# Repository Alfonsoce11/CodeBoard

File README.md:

# CodeBoard
A keyboard specially made for coding with quicker access to common characters. After making [CodePad](https://github.com/Alfonsoce11/CodePad/) I figured the next logical thing to do was to make a full keyboard for coding.
| Assembly | Exploded View |
|--|--|
|  |  |

# Layout

I chose this layout so that I could keep the normal keyboard layout while also optimizing for coding. It has keys I often use while coding to the right of the main part of the keyboard, similar to a numpad but for coding. The brackets and quotes type both characters and put the curser between the characters. The angle brackets don't because they are more commonly used for conditions rather than brackets in coding.

I wrote the firmware using KMK.

# Case

The case consists of 3 parts: the bottom, the plate, and the top part. It uses M3x16mm screws and heat-set inserts to hold the 3 parts together.
| Bottom | Plate | Top |
|--------|-------|-----|
|  |  |  |

Heres an assembly of the case:

I made the case using OnShape.

# PCB

**Schematic:**

**PCB:**

**3D PCB:**

I made the PCB on KiCAD and learned how to create a key matrix.

# More Views

# BOM
|Item                           |Quantity|Price |Link                                                                                                                                                                                                                                                           |
|-------------------------------|--------|------|---------------------------------------------------------------------------------------------------------------------------------------------------------------------------------------------------------------------------------------------------------------|
|Raspberry Pi Pico              |1       |$4.00 |https://vilros.com/products/raspberry-pi-pico                                                                                                                                                                                                                  |
|Brown 90 PCS Cherry MX Switches|1       |$16.01|https://www.aliexpress.com/item/3256807797357274.html?spm=a2g0o.cart.0.0.7b1f38daq82dup&mp=1&pdp_npi=5%40dis%21USD%21USD%2034.20%21USD%2016.01%21%21USD%2016.01%21%21%21%402101c59517507203853198392e81ba%2112000043155900936%21ct%21US%216400114757%21%211%210|
|M3x16mm 50 PCS Screws          |1       |$3.10 |https://www.aliexpress.com/item/2251832772825104.html?spm=a2g0o.cart.0.0.7b1f38daq82dup&mp=1&pdp_npi=5%40dis%21USD%21USD%203.10%21USD%203.10%21%21USD%203.10%21%21%21%402101c59517507203853198392e81ba%2166368903760%21ct%21US%216400114757%21%211%210         |
|Heat Set Inserts               |1       |$6.55 |https://www.aliexpress.com/item/2255800046543591.html?spm=a2g0o.cart.0.0.7b1f38daq82dup&mp=1&pdp_npi=5%40dis%21USD%21USD%207.10%21USD%206.55%21%21USD%206.55%21%21%21%402101c59517507203853198392e81ba%2110000000945302188%21ct%21US%216400114757%21%211%210   |
|100 PCS Diodes                 |1       |$1.46 |https://www.aliexpress.com/item/2255799955957794.html?spm=a2g0o.cart.0.0.7b1f38daq82dup&mp=1&pdp_npi=5%40dis%21USD%21USD%201.46%21USD%201.46%21%21USD%201.46%21%21%21%402101c59517507203853198392e81ba%2110000000428321629%21ct%21US%216400114757%21%211%210   |
|100 PCS Black Keycaps          |1       |$22.03|https://www.aliexpress.com/item/3256805981338445.html?spm=a2g0o.cart.0.0.7b1f38daq82dup&mp=1&pdp_npi=5%40dis%21USD%21USD%2030.60%21USD%2022.03%21%21USD%2022.03%21%21%21%402101c59517507203853198392e81ba%2112000036085970239%21ct%21US%216400114757%21%211%210|
|2u Cherry Stabilizers          |2       |$1.55 |https://www.aliexpress.com/item/2251832678459913.html?spm=a2g0o.cart.0.0.7b1f38daq82dup&mp=1&pdp_npi=5%40dis%21USD%21USD%201.87%21USD%201.55%21%21USD%201.55%21%21%21%402101c59517507203853198392e81ba%2112000036652220667%21ct%21US%216400114757%21%212%210   |
|6u Cherry Stabilizer           |1       |$1.66 |https://www.aliexpress.com/item/2251832678459913.html?spm=a2g0o.cart.0.0.7b1f38daq82dup&mp=1&pdp_npi=5%40dis%21USD%21USD%202.00%21USD%201.66%21%21USD%201.66%21%21%21%402101c59517507203853198392e81ba%2112000036652220673%21ct%21US%216400114757%21%211%210   |
|PCB                            |5       |$25.11|https://jlcpcb.com/                                                                                                                                                                                                                                            |
|TOTAL                          |        |$81.47|                                                                                                                                                                                                                                                               |

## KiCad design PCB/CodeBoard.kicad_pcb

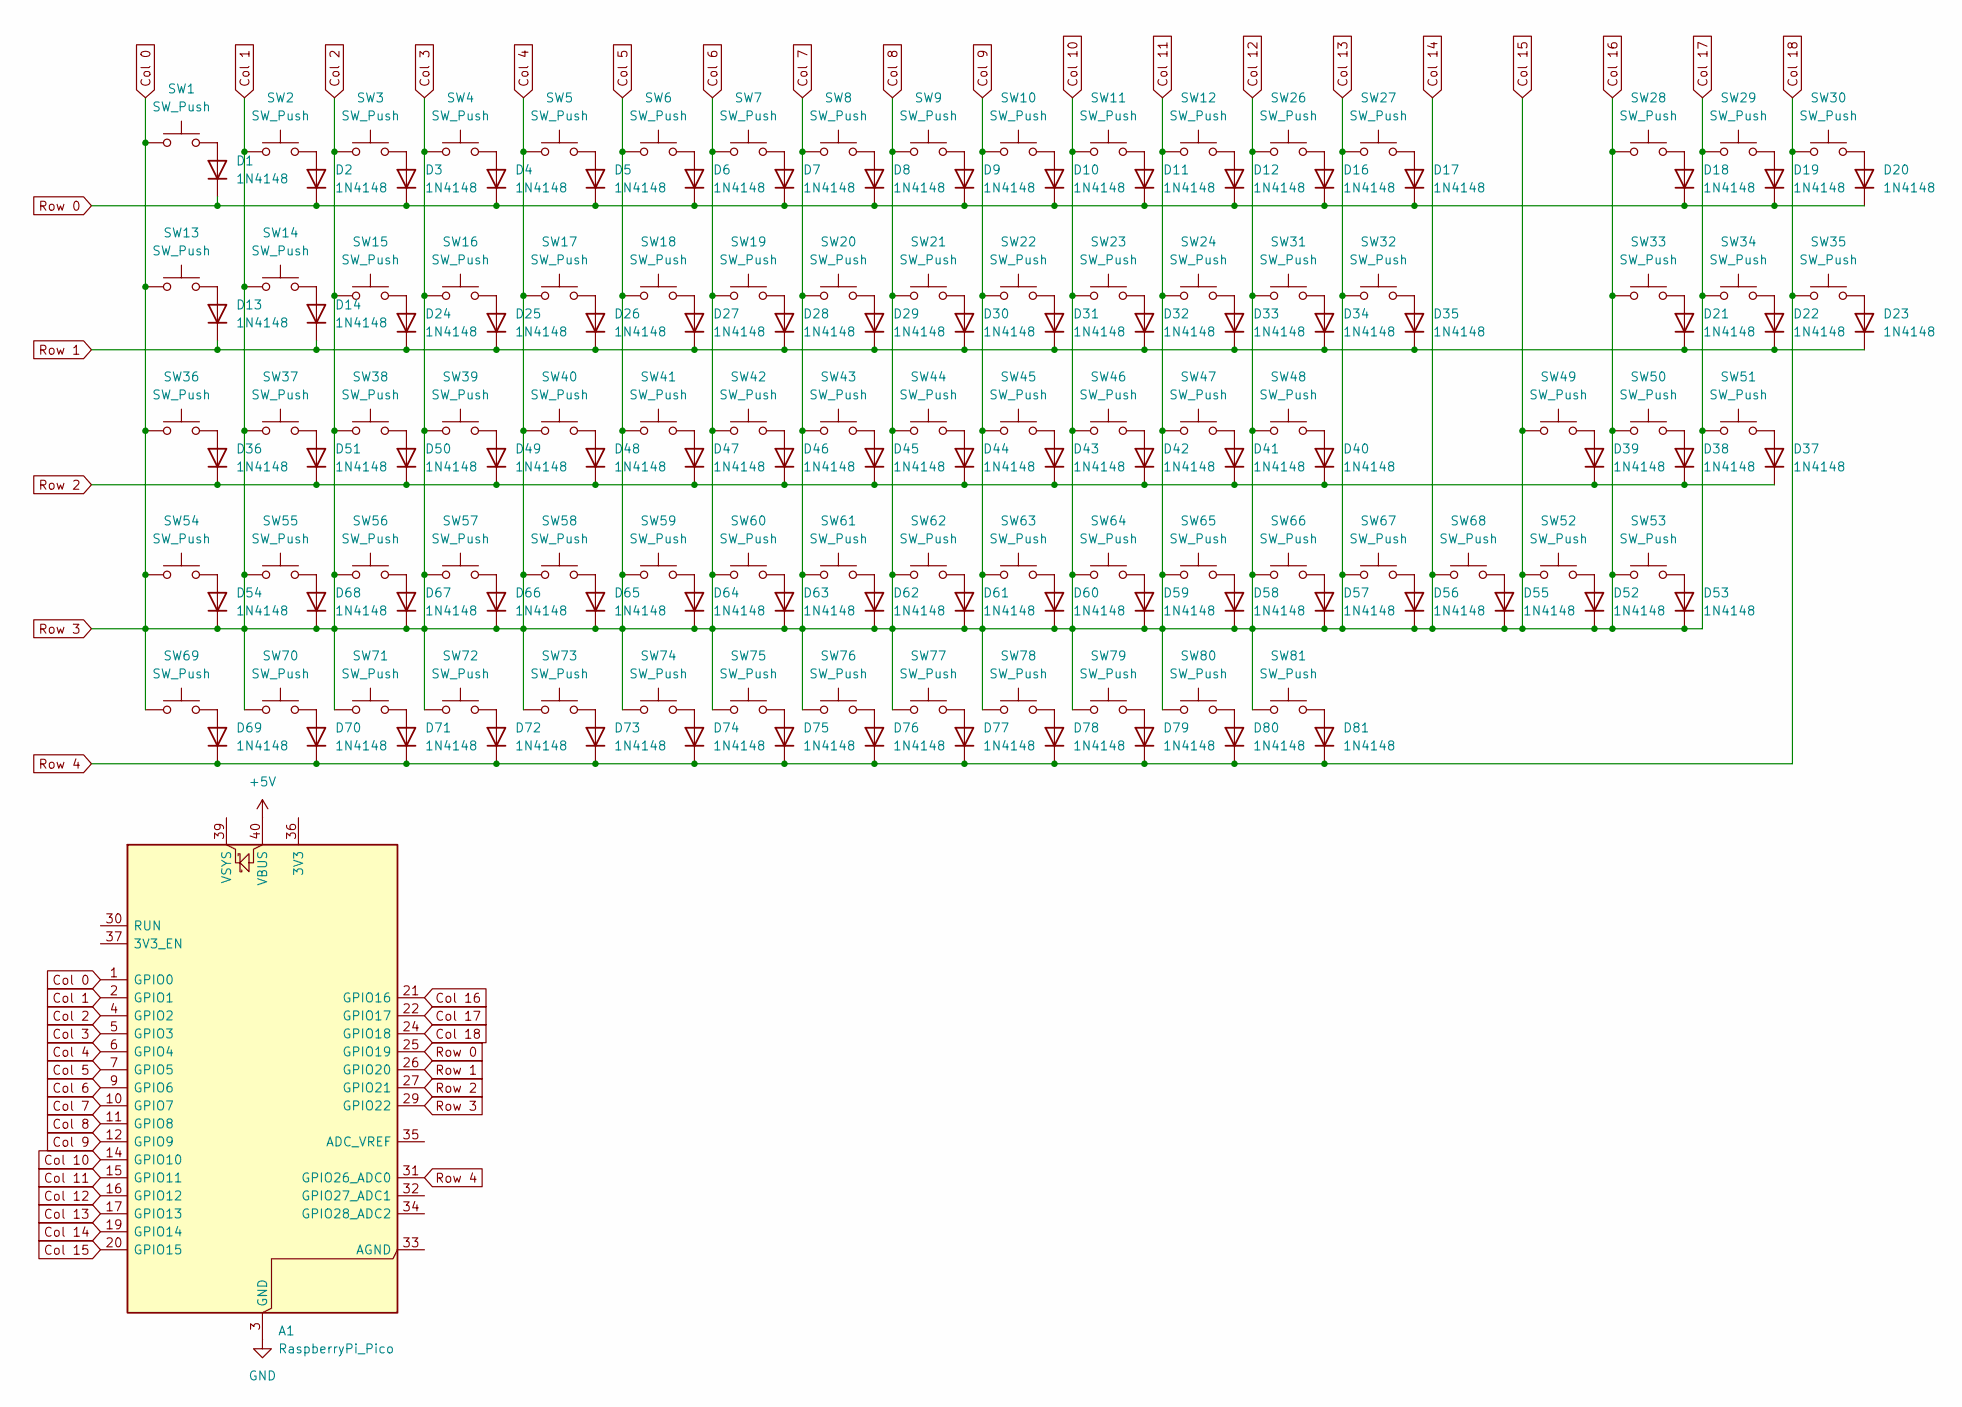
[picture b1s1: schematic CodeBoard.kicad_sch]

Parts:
A1: RaspberryPi_Pico; RaspberryPi_Pico_Common_Unspecified
D1, D2, D3, D4, D5, D6, D7, D8, D9, D10, D11, D12, D13, D14, D16, D17, D18, D19, D20, D21, D22, D23, D24, D25, D26, D27, D28, D29, D30, D31, D32, D33, D34, D35, D36, D37, D38, D39, D40, D41, D42, D43, D44, D45, D46, D47, D48, D49, D50, D51, D52, D53, D54, D55, D56, D57, D58, D59, D60, D61, D62, D63, D64, D65, D66, D67, D68, D69, D70, D71, D72, D73, D74, D75, D76, D77, D78, D79, D80, D81: 1N4148; D_DO-35_SOD27_P7.62mm_Horizontal
SW1, SW2, SW3, SW4, SW5, SW6, SW7, SW8, SW9, SW10, SW11, SW12, SW13, SW14, SW15, SW16, SW17, SW18, SW19, SW20, SW21, SW22, SW23, SW24, SW26, SW27, SW28, SW29, SW30, SW31, SW32, SW33, SW34, SW35, SW36, SW37, SW38, SW39, SW40, SW41, SW42, SW43, SW44, SW45, SW46, SW47, SW48, SW49, SW50, SW51, SW52, SW53, SW54, SW55, SW56, SW57, SW58, SW59, SW60, SW61, SW62, SW63, SW64, SW65, SW66, SW67, SW68, SW69, SW70, SW71, SW72, SW73, SW74, SW75, SW76, SW77, SW78, SW79, SW80, SW81: SW_Push; SW_Cherry_MX_1.00u_PCB

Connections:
+5V: A1.40 (VBUS)
Col 0: A1.1 (GPIO0), A1.2 (GPIO1), A1.4 (GPIO2), A1.5 (GPIO3), A1.6 (GPIO4), A1.7 (GPIO5), A1.9 (GPIO6), A1.10 (GPIO7), A1.11 (GPIO8), A1.12 (GPIO9), A1.14 (GPIO10), A1.15 (GPIO11), A1.16 (GPIO12), A1.17 (GPIO13), A1.19 (GPIO14), A1.20 (GPIO15), A1.21 (GPIO16), A1.22 (GPIO17), A1.29 (GPIO22), D52.1 (K), D53.1 (K), D54.1 (K), D55.1 (K), D56.1 (K), D57.1 (K), D58.1 (K), D59.1 (K), D60.1 (K), D61.1 (K), D62.1 (K), D63.1 (K), D64.1 (K), D65.1 (K), D66.1 (K), D67.1 (K), D68.1 (K), SW1.1, SW2.1, SW3.1, SW4.1, SW5.1, SW6.1, SW7.1, SW8.1, SW9.1, SW10.1, SW11.1, SW12.1, SW13.1, SW14.1, SW15.1, SW16.1, SW17.1, SW18.1, SW19.1, SW20.1, SW21.1, SW22.1, SW23.1, SW24.1, SW26.1, SW27.1, SW28.1, SW29.1, SW31.1, SW32.1, SW33.1, SW34.1, SW36.1, SW37.1, SW38.1, SW39.1, SW40.1, SW41.1, SW42.1, SW43.1, SW44.1, SW45.1, SW46.1, SW47.1, SW48.1, SW49.1, SW50.1, SW51.1, SW52.1, SW53.1, SW54.1, SW55.1, SW56.1, SW57.1, SW58.1, SW59.1, SW60.1, SW61.1, SW62.1, SW63.1, SW64.1, SW65.1, SW66.1, SW67.1, SW68.1, SW69.1, SW70.1, SW71.1, SW72.1, SW73.1, SW74.1, SW75.1, SW76.1, SW77.1, SW78.1, SW79.1, SW80.1, SW81.1
Col 18: A1.24 (GPIO18), A1.31 (GPIO26_ADC0), D69.1 (K), D70.1 (K), D71.1 (K), D72.1 (K), D73.1 (K), D74.1 (K), D75.1 (K), D76.1 (K), D77.1 (K), D78.1 (K), D79.1 (K), D80.1 (K), D81.1 (K), SW30.1, SW35.1
GND: A1.3 (GND), A1.8 (GND), A1.13 (GND), A1.18 (GND), A1.23 (GND), A1.28 (GND), A1.38 (GND)
unnamed: D1.2 (A), SW1.2
unnamed: D2.2 (A), SW2.2
unnamed: D3.2 (A), SW3.2
unnamed: D4.2 (A), SW4.2
unnamed: D5.2 (A), SW5.2
unnamed: D6.2 (A), SW6.2
unnamed: D7.2 (A), SW7.2
unnamed: D8.2 (A), SW8.2
unnamed: D9.2 (A), SW9.2
unnamed: D10.2 (A), SW10.2
unnamed: D11.2 (A), SW11.2
unnamed: D12.2 (A), SW12.2
unnamed: D13.2 (A), SW13.2
unnamed: D14.2 (A), SW14.2
unnamed: D16.2 (A), SW26.2
unnamed: D17.2 (A), SW27.2
unnamed: D18.2 (A), SW28.2
unnamed: D19.2 (A), SW29.2
unnamed: D20.2 (A), SW30.2
unnamed: D21.2 (A), SW33.2
unnamed: D22.2 (A), SW34.2
unnamed: D23.2 (A), SW35.2
unnamed: D24.2 (A), SW15.2
unnamed: D25.2 (A), SW16.2
unnamed: D26.2 (A), SW17.2
unnamed: D27.2 (A), SW18.2
unnamed: D28.2 (A), SW19.2
unnamed: D29.2 (A), SW20.2
unnamed: D30.2 (A), SW21.2
unnamed: D31.2 (A), SW22.2
unnamed: D32.2 (A), SW23.2
unnamed: D33.2 (A), SW24.2
unnamed: D34.2 (A), SW31.2
unnamed: D35.2 (A), SW32.2
unnamed: D36.2 (A), SW36.2
unnamed: D37.2 (A), SW51.2
unnamed: D38.2 (A), SW50.2
unnamed: D39.2 (A), SW49.2
unnamed: D40.2 (A), SW48.2
unnamed: D41.2 (A), SW47.2
unnamed: D42.2 (A), SW46.2
unnamed: D43.2 (A), SW45.2
unnamed: D44.2 (A), SW44.2
unnamed: D45.2 (A), SW43.2
unnamed: D46.2 (A), SW42.2
unnamed: D47.2 (A), SW41.2
unnamed: D48.2 (A), SW40.2
unnamed: D49.2 (A), SW39.2
unnamed: D50.2 (A), SW38.2
unnamed: D51.2 (A), SW37.2
unnamed: D52.2 (A), SW52.2
unnamed: D53.2 (A), SW53.2
unnamed: D54.2 (A), SW54.2
unnamed: D55.2 (A), SW68.2
unnamed: D56.2 (A), SW67.2
unnamed: D57.2 (A), SW66.2
unnamed: D58.2 (A), SW65.2
unnamed: D59.2 (A), SW64.2
unnamed: D60.2 (A), SW63.2
unnamed: D61.2 (A), SW62.2
unnamed: D62.2 (A), SW61.2
unnamed: D63.2 (A), SW60.2
unnamed: D64.2 (A), SW59.2
unnamed: D65.2 (A), SW58.2
unnamed: D66.2 (A), SW57.2
unnamed: D67.2 (A), SW56.2
unnamed: D68.2 (A), SW55.2
unnamed: D69.2 (A), SW69.2
unnamed: D70.2 (A), SW70.2
unnamed: D71.2 (A), SW71.2
unnamed: D72.2 (A), SW72.2
unnamed: D73.2 (A), SW73.2
unnamed: D74.2 (A), SW74.2
unnamed: D75.2 (A), SW75.2
unnamed: D76.2 (A), SW76.2
unnamed: D77.2 (A), SW77.2
unnamed: D78.2 (A), SW78.2
unnamed: D79.2 (A), SW79.2
unnamed: D80.2 (A), SW80.2
unnamed: D81.2 (A), SW81.2
Row 0: A1.25 (GPIO19), D1.1 (K), D2.1 (K), D3.1 (K), D4.1 (K), D5.1 (K), D6.1 (K), D7.1 (K), D8.1 (K), D9.1 (K), D10.1 (K), D11.1 (K), D12.1 (K), D16.1 (K), D17.1 (K), D18.1 (K), D19.1 (K), D20.1 (K)
Row 1: A1.26 (GPIO20), D13.1 (K), D14.1 (K), D21.1 (K), D22.1 (K), D23.1 (K), D24.1 (K), D25.1 (K), D26.1 (K), D27.1 (K), D28.1 (K), D29.1 (K), D30.1 (K), D31.1 (K), D32.1 (K), D33.1 (K), D34.1 (K), D35.1 (K)
Row 2: A1.27 (GPIO21), D36.1 (K), D37.1 (K), D38.1 (K), D39.1 (K), D40.1 (K), D41.1 (K), D42.1 (K), D43.1 (K), D44.1 (K), D45.1 (K), D46.1 (K), D47.1 (K), D48.1 (K), D49.1 (K), D50.1 (K), D51.1 (K)

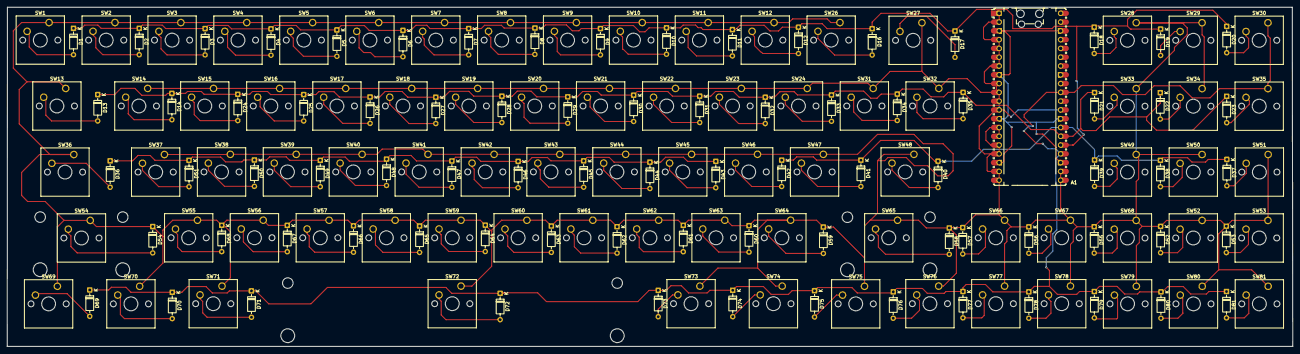
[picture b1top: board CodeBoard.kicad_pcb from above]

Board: 2 copper layers, 371.7 x 98.1 mm, 161 parts (0 on the bottom side), 86 nets.

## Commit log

2025-06-29 Update fp-info-cache
